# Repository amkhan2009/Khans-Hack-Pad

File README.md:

Khan Pad
The Khan is Board of typing is a 4 key macropad/keyboard with 2 EC11 style rotary encoders.

Features:
3D printable with screws and heatset inserts
EC11 Rotary encoders for rotational action AND they serve as switches/keys
4 fully programmable keys in a matrix
CAD Model:
4 heatset inserts and 4 M3 screws are used to keep everything together

The model consists of a bottom case, a plate, and a bracket for the top, so the key switches themselves are less exposed.

CAD

PCB / Schematic
The PCB as well as the schematic is pictured below:

Schematic

PCB

BOM:
Here is everything needed to make the BoardPad

4x Cherry MX Switches
4x DSA Keycaps
4x M3x5x4 Heatset inserts
4X M3x12mm SHCS Bolts
11x 1N4148 DO-35 Diodes.
2x EC11 Rotary Encoder
1x XIAO RP2040
1x Case (3 3D printed parts)
2x Rotary Encoder Dials
1x PCB

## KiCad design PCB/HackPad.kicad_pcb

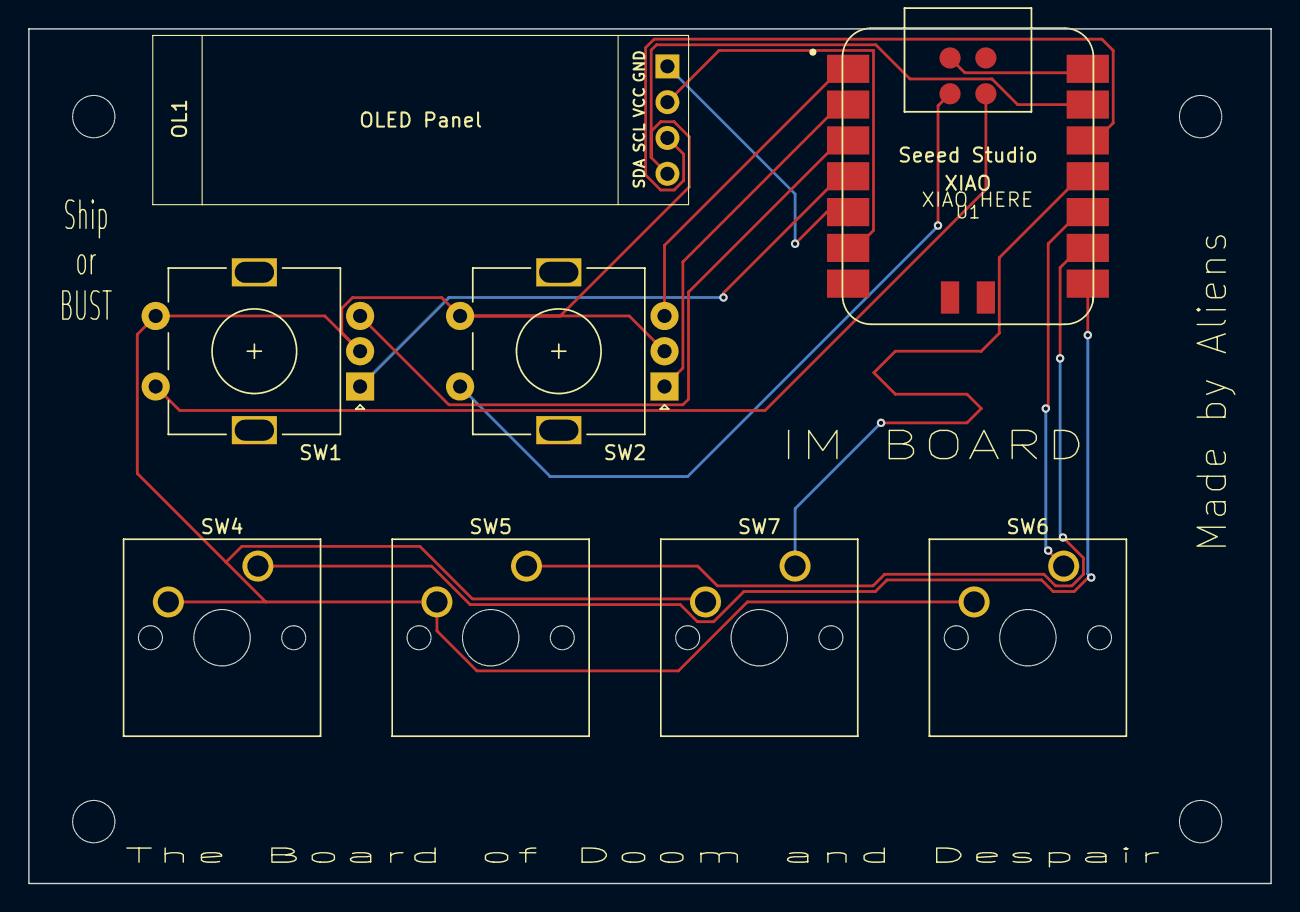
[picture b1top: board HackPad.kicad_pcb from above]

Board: 2 copper layers, 88.1 x 60.6 mm, 8 parts (0 on the bottom side), 9 nets.

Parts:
OL1: OLED; SSD1306-0.91-OLED-4pin-128x32
SW1, SW2: RotaryEncoder_Switch; RotaryEncoder_Alps_EC11E-Switch_Vertical_H20mm
SW4, SW5, SW6, SW7: SW_Push; SW_Cherry_MX_1.00u_PCB
U1: Seeed Studio XIAO SAMD21; XIAO-SAMD21-RP2040-14P-2.54-21X17.8MM (Seeeduino XIAO)

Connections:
+5V: U1.14 (5V), U1.15 (5V)
GND: OL1.4 (GND), SW1.C, SW1.S1, SW2.C, SW2.S1, SW4.2, SW5.2, SW6.2, SW7.2, U1.13 (GND)
unnamed: OL1.2 (SCL), U1.6 (PA9_A5_D5_SCL)
unnamed: OL1.1 (SDA), U1.5 (PA8_A4_D4_SDA)
unnamed: OL1.3 (VCC), U1.12 (3V3)
unnamed: SW6.1, U1.10 (PA5_A9_D9_MISO)
unnamed: SW5.1, U1.9 (PA7_A8_D8_SCK)
unnamed: SW1.B, U1.3 (PA10_A2_D2)
unnamed: SW1.A, U1.4 (PA11_A3_D3)

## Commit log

2026-02-19 Add README for Khan Pad macropad project
    Added detailed description of the Khan Pad, including features, CAD model, PCB schematic, and BOM.
2026-02-19 Add PCB and schematic images to README
    Added images for PCB and schematic in the README.
2026-02-19 Create CAD
2026-02-19 Create Top Part
2026-02-19 Add Middle Part to CAD project
2026-02-19 Create CAD photos
2026-02-19 Rename Screenshot 2026-02-18 222736.png to CAD Overview
2026-02-19 Rename Screenshot 2026-02-18 222742.png to CAD Top Overview
2026-02-19 Rename Screenshot 2026-02-18 222849.png to PCB
2026-02-19 Rename Screenshot 2026-02-18 223324.png to Schematic
2026-02-21 Refactor StopwatchScreen for better display management
    Refactor StopwatchScreen initialization and update logic, improving display handling and timer updates.
2026-02-25 Update print statement from 'Hello' to 'Goodbye'
2026-02-25 Enhance README with CAD images and terminology fixes
    Updated the README to include additional CAD images and corrected terminology from 'macpad' to 'BoardPad'.
2026-02-25 Revise PCB and schematic images in README
    Updated images and labels for PCB and schematic sections.
2026-02-25 Create PCB
2026-02-25 Rename Screenshot 2026-02-24 200830.png to CAD Overview
